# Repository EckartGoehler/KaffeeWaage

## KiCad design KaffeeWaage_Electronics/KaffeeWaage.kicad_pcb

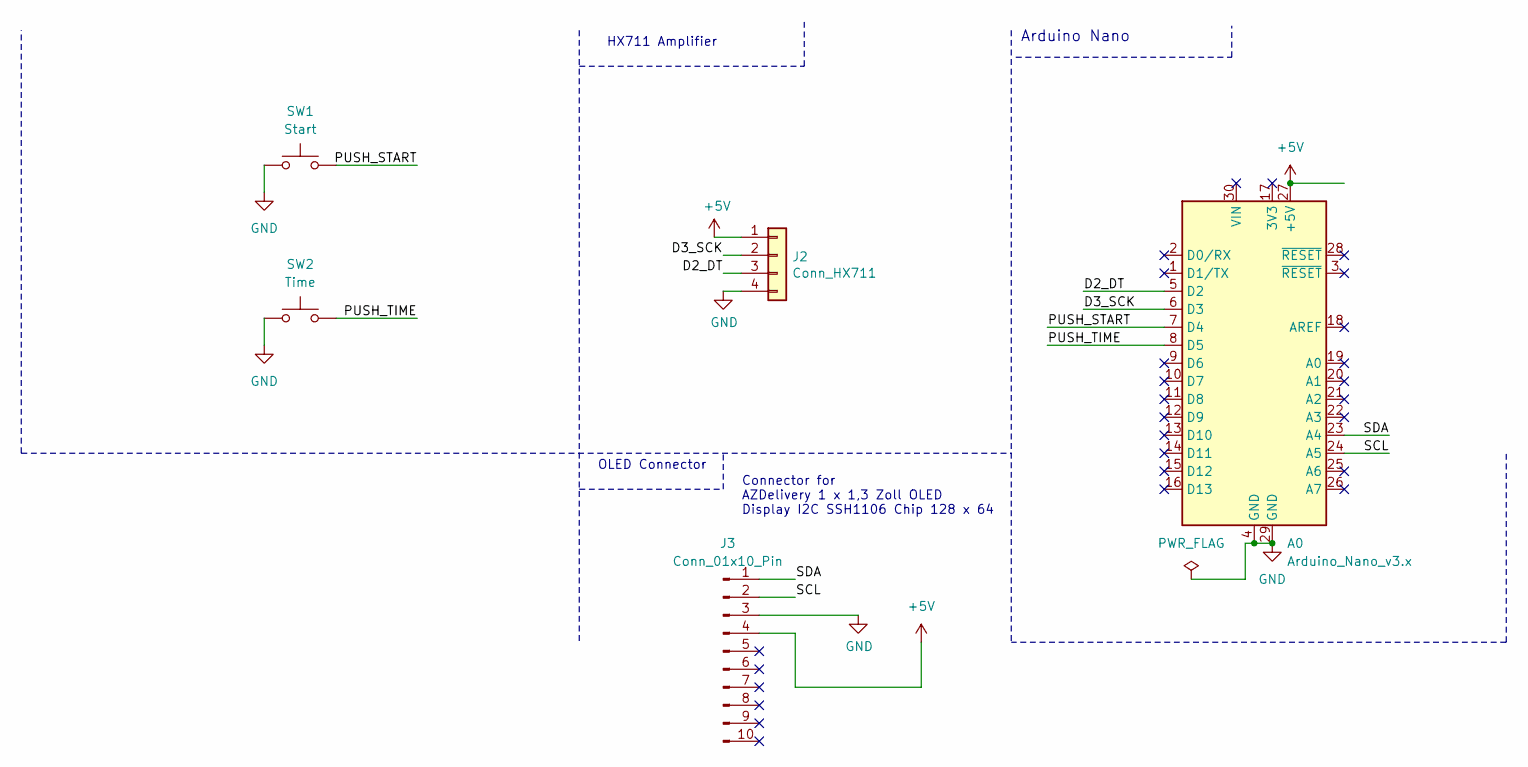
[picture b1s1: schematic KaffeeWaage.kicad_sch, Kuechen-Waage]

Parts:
A0: Arduino_Nano_v3.x; Arduino_Nano
J2: Conn_HX711; PinHeader_1x04_P2.54mm_Vertical
J3: Conn_01x10_Pin; PinHeader_2x05_P2.54mm_Vertical
SW1: Start; SW_PUSH-12mm
SW2: Time; SW_PUSH-12mm

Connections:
+5V: A0.27 (+5V), J2.1, J3.4
/D2_DT: A0.5 (D2), J2.3
/D3_SCK: A0.6 (D3), J2.2
/PUSH_START: A0.7 (D4), SW1.2
/PUSH_TIME: A0.8 (D5), SW2.2
/SCL: A0.24 (A5), J3.2
/SDA: A0.23 (A4), J3.1
GND: A0.4 (GND), A0.29 (GND), J2.4, J3.3, SW1.1, SW2.1

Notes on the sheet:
Connector for AZDelivery 1 x 1,3 Zoll OLED Display I2C SSH1106 Chip 128 x 64
OLED Connector
HX711 Amplifier
Arduino Nano

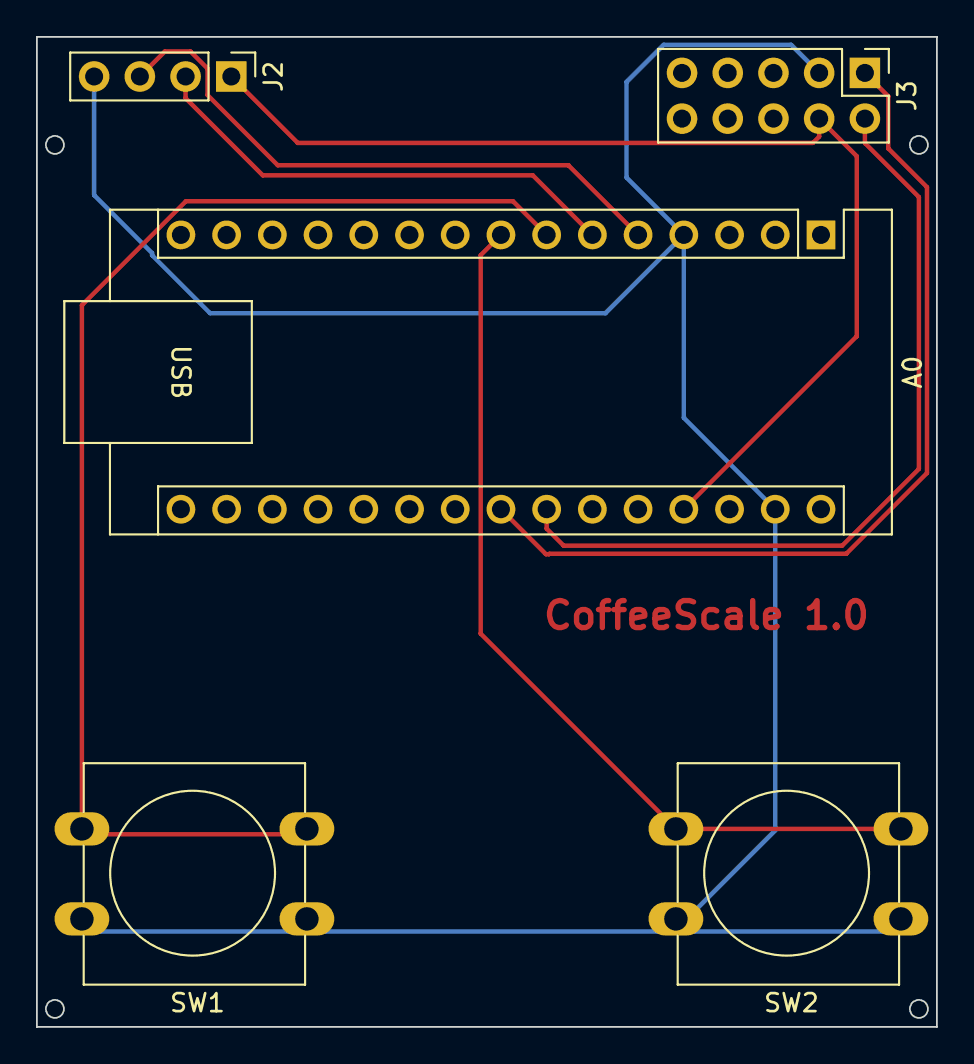
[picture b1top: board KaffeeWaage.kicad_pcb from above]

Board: 2 copper layers, 50.0 x 55.0 mm, 5 parts (0 on the bottom side), 8 nets.

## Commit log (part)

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2025-10-12 Add: current state of coffeescale. Electronics up and running, CAD in printing, SW draft as scale but no button or time support
2025-10-13 Fixes of top shell: - proper button holes - smaller display mounting - more space for scale mounting
2025-10-13 Change: cound corners for smooth appearence
2025-10-14 Fix of wrong mounting points and sizes for - button holes - scale mounting holes and width - display mounting pin sizes and positions
2025-10-18 Add: timer button reaction
2025-10-18 Add sleep button functionality - switches off the display and re-tares
2025-10-18 Nicer output
2025-10-18 Add: clamps, buttons, scale-basket
2025-10-25 Fix: proper post comma digits for wheight
2025-10-25 change: longer time button debounce window of 0.5s
